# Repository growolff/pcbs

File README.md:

# pcbs
Documentación de PCBs de proyectos personales, para acceso y repositoreo remoto.

* UsainBot v1

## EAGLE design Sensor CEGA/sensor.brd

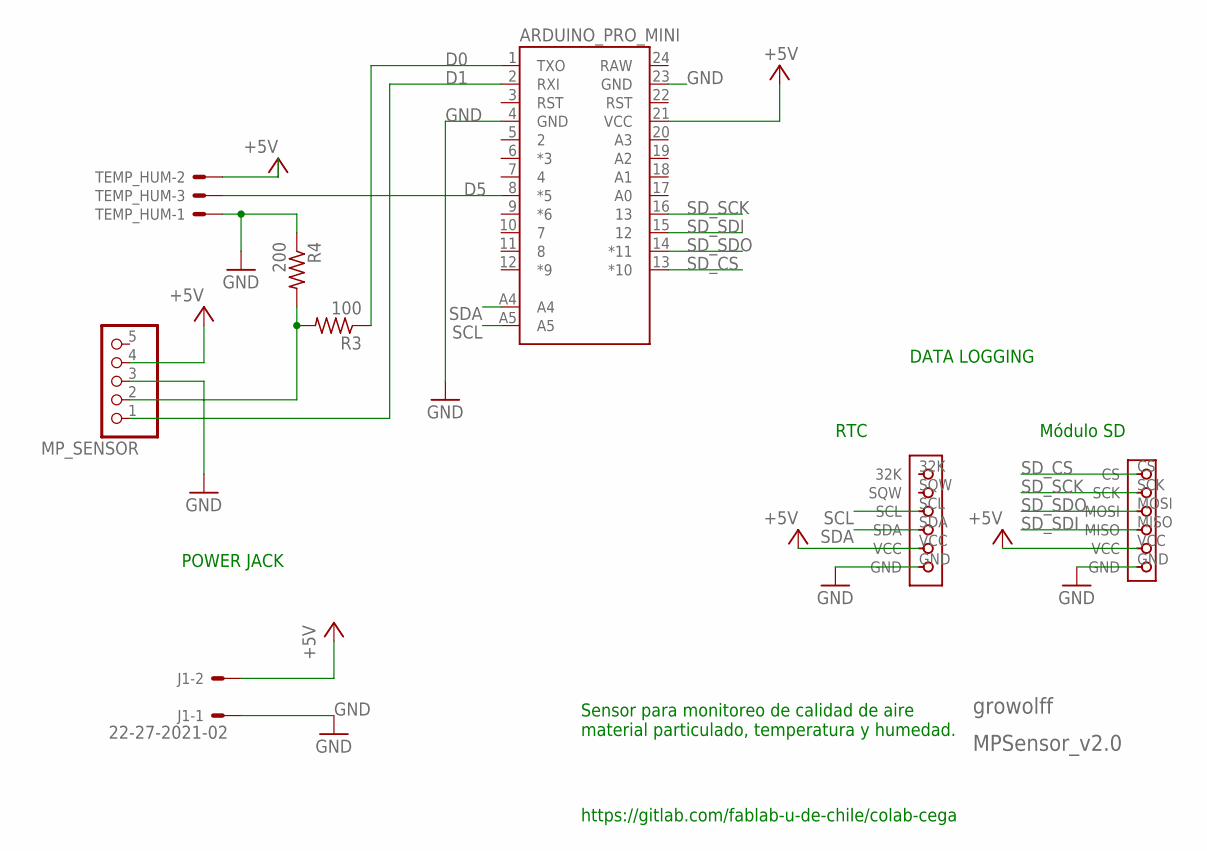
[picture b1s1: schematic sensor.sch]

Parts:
ARDUINO_PRO_MINI: PRO_MINI_CEGAPRO_MINI_MOD; ARDUINO_PRO_MINI_MOD
J1: 22-27-2021-02; 6410-02
MP_SENSOR: PINHD-1X5; 1X05
R3: 100; 0207/7
R4: 200; 0207/7
RTC: DS3231_RTC
SD_READER: MICRO_SD_READER
TEMP_HUM: 22-27-2031-03; 6410-03

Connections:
+5V: ARDUINO_PRO_MINI.21 (VCC), J1.2, MP_SENSOR.4, RTC.VCC, SD_READER.VCC, TEMP_HUM.2
D0: ARDUINO_PRO_MINI.1 (TXO), R3.1
D1: ARDUINO_PRO_MINI.2 (RXI), MP_SENSOR.1
D5: ARDUINO_PRO_MINI.8 (*5), TEMP_HUM.3
GND: ARDUINO_PRO_MINI.4 (GND), ARDUINO_PRO_MINI.23 (GND), J1.1, MP_SENSOR.3, R4.1, RTC.GND, SD_READER.GND, TEMP_HUM.1
unnamed: MP_SENSOR.2, R3.2, R4.2
RAW: ARDUINO_PRO_MINI.24 (RAW)
SCL: ARDUINO_PRO_MINI.A5, RTC.SCL
SDA: ARDUINO_PRO_MINI.A4, RTC.SDA
SD_CS: ARDUINO_PRO_MINI.13 (*10), SD_READER.CS
SD_SCK: ARDUINO_PRO_MINI.16 (13), SD_READER.SCK
SD_SDI: ARDUINO_PRO_MINI.15 (12), SD_READER.MISO
SD_SDO: ARDUINO_PRO_MINI.14 (*11), SD_READER.MOSI

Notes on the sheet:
growolff
https://gitlab.com/fablab-u-de-chile/colab-cega
Sensor para monitoreo de calidad de aire material particulado, temperatura y humedad.
MPSensor_v2.0
Módulo SD
DATA LOGGING
RTC
POWER JACK

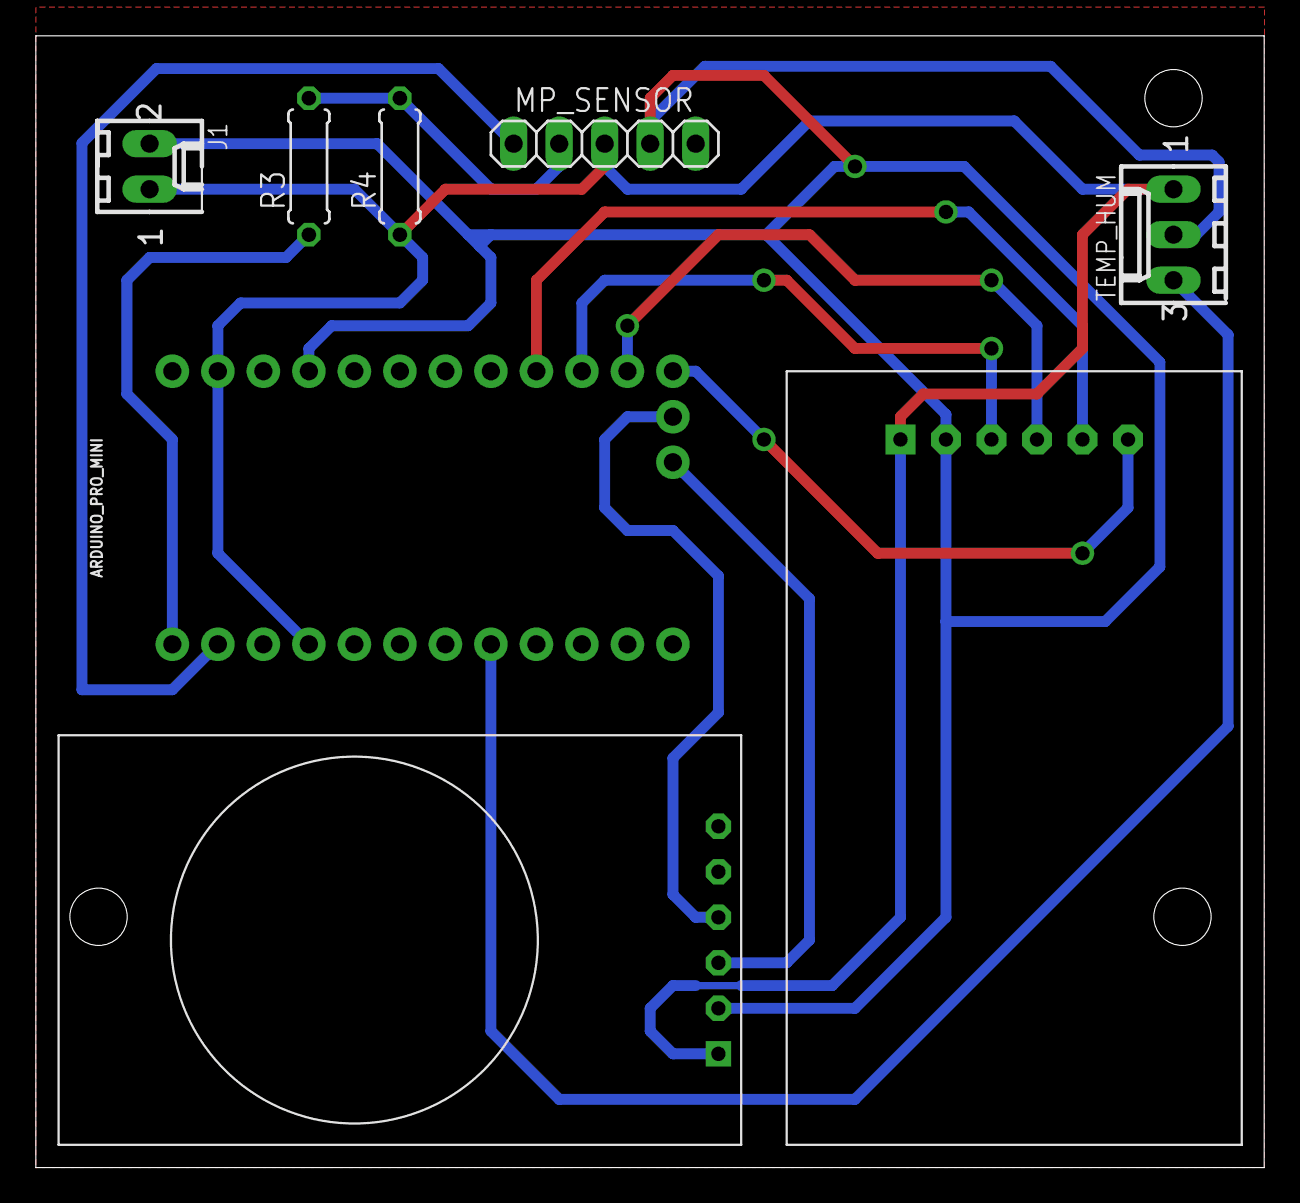
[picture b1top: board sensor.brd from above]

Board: 2 copper layers, 68.6 x 63.2 mm, 8 parts (0 on the bottom side), 12 nets.

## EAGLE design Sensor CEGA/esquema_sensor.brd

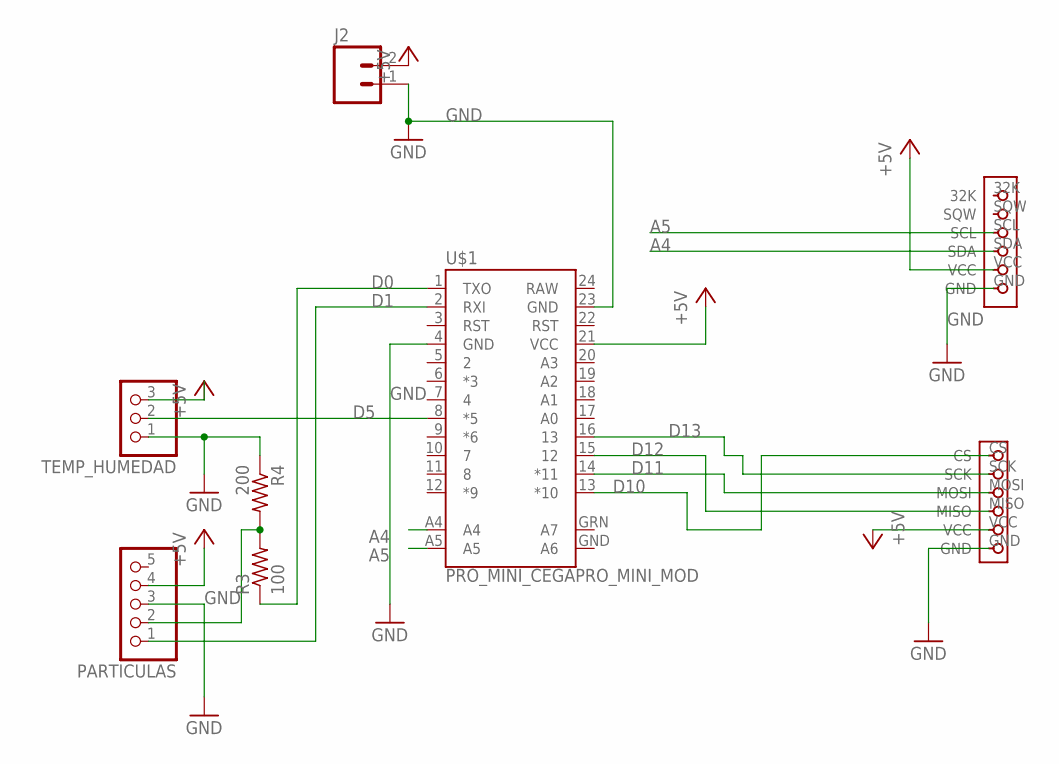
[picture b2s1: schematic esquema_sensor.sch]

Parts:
J2: M025MM; SCREWTERMINAL-5MM-2
PARTICULAS: PINHD-1X5; 1X05
R3: 100; 0207/7
R4: 200; 0207/7
RTC: DS3231_RTC
SD_READER: MICRO_SD_READER
TEMP_HUMEDAD: PINHD-1X3; 1X03
U$1: PRO_MINI_CEGAPRO_MINI_MOD; ARDUINO_PRO_MINI_MOD

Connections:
+5V: J2.2, PARTICULAS.4, RTC.VCC, SD_READER.VCC, TEMP_HUMEDAD.3, U$1.21 (VCC)
A4: RTC.SDA, U$1.A4
A5: RTC.SCL, U$1.A5
D0: R3.1, U$1.1 (TXO)
D1: PARTICULAS.1, U$1.2 (RXI)
D5: TEMP_HUMEDAD.2, U$1.8 (*5)
D10: SD_READER.CS, U$1.13 (*10)
D11: SD_READER.MOSI, U$1.14 (*11)
D12: SD_READER.MISO, U$1.15 (12)
D13: SD_READER.SCK, U$1.16 (13)
GND: J2.1, PARTICULAS.3, R4.1, RTC.GND, SD_READER.GND, TEMP_HUMEDAD.1, U$1.4 (GND), U$1.23 (GND)
unnamed: PARTICULAS.2, R3.2, R4.2
RAW: U$1.24 (RAW)

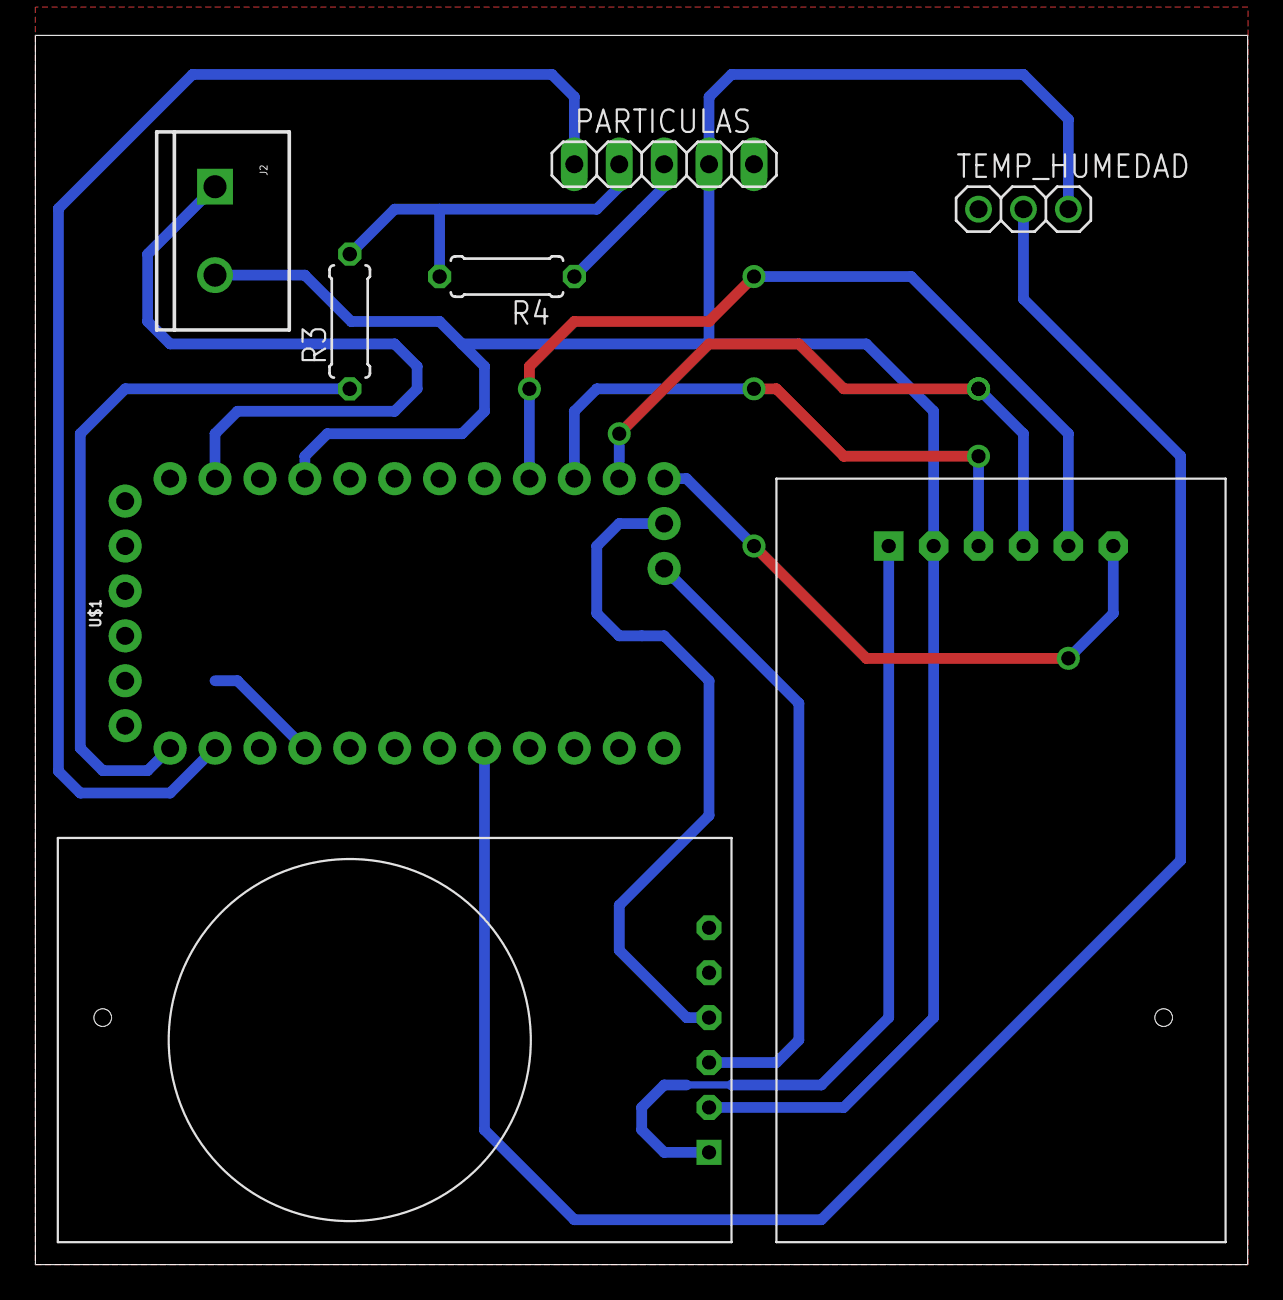
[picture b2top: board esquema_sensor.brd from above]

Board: 2 copper layers, 68.6 x 69.5 mm, 8 parts (0 on the bottom side), 12 nets.

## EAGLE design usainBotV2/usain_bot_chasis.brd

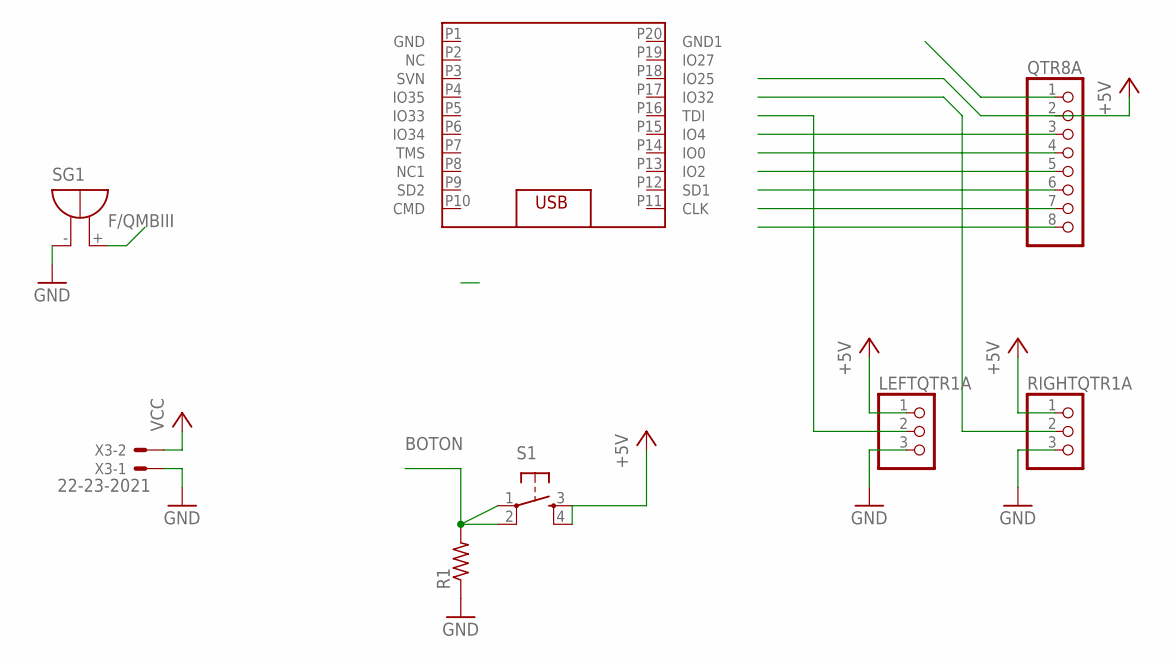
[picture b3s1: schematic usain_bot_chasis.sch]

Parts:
ESP32: ESP32_MINI_KIT
LEFTQTR1A: PINHD-1X3; 1X03
QTR8A: PINHD-1X8BIG; 1X08-BIG
R1: R-US_0207/7; 0207/7
RIGHTQTR1A: PINHD-1X3; 1X03
S1: TAC_SWITCHPTH; TACTILE-PTH
SG1: F/QMBIII
X3: 22-23-2021

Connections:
+5V: LEFTQTR1A.1, QTR8A.2, RIGHTQTR1A.1, S1.3, S1.4
BOTON: R1.2, S1.1, S1.2
GND: LEFTQTR1A.3, R1.1, RIGHTQTR1A.3, SG1.- (+), X3.1
VCC: X3.2

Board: 2 copper layers, 8 parts (0 on the bottom side), 3 nets, no tracks yet.

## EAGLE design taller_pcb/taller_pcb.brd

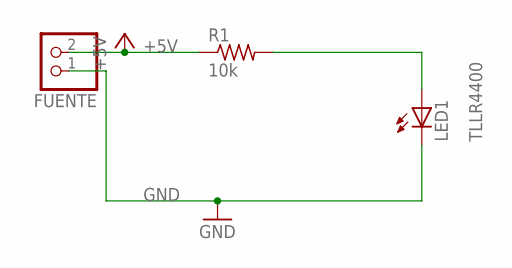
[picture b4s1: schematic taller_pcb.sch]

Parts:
FUENTE: PINHD-1X2; 1X02
LED1: TLLR4400; LED3MM
R1: 10k; 0309/12

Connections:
+5V: FUENTE.2, R1.1
GND: FUENTE.1, LED1.K (C)
unnamed: LED1.A, R1.2

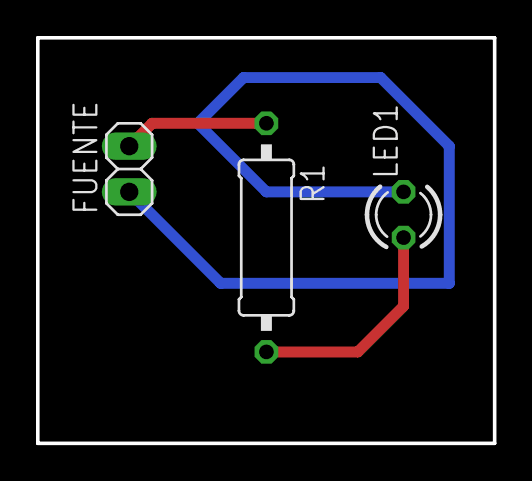
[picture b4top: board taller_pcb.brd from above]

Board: 2 copper layers, 25.4 x 22.5 mm, 3 parts (0 on the bottom side), 3 nets.

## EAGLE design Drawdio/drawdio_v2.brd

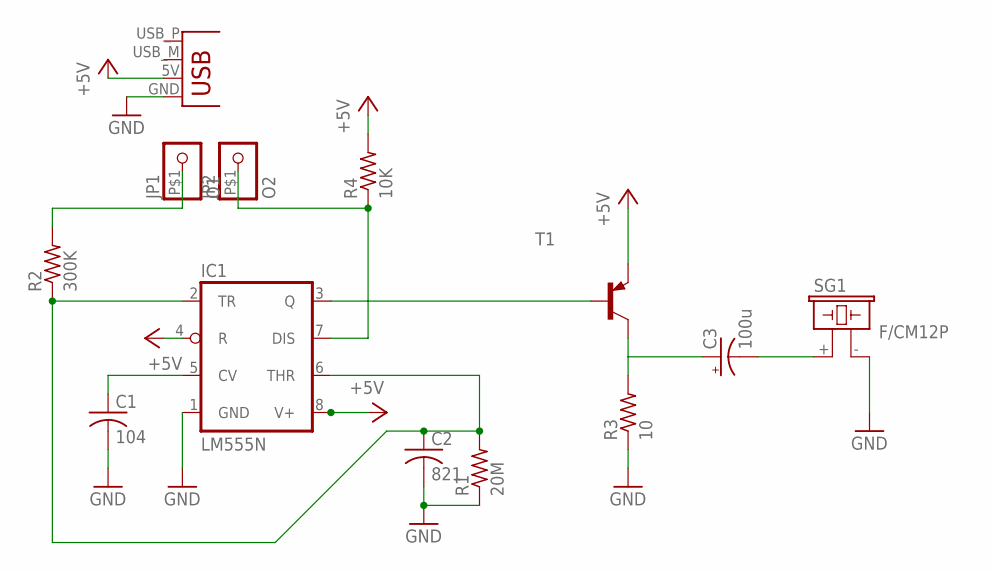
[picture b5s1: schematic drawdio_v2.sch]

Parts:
C1: 104; C025-030X050
C2: 821; C050-024X044
C3: 100u; E2,5-6E
IC1: LM555N; DIL08
JP1: O1; 1X1-BIGPOGO
JP2: O2; 1X1-BIGPOGO
R1: 20M; 0207/7
R2: 300K; 0207/7
R3: 10; 0207/7
R4: 10K; 0207/7
SG1: F/CM12P
T1: MPS2907A-PNP-TO92-CBE; TO92-CBE
X1: USBPCB; USB-A-PCB

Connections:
+5V: IC1.4 (R), IC1.8 (V+), R4.2, T1.E, X1.5V (VBUS)
GND: C1.2, C2.2, IC1.1 (GND), R1.1, R3.1, SG1.- (2), X1.GND
unnamed: C1.1, IC1.5 (CV)
unnamed: C2.1, IC1.2 (TR), IC1.6 (THR), R1.2, R2.1
unnamed: C3.-, SG1.+ (1)
unnamed: JP1.P$1, R2.2
unnamed: IC1.7 (DIS), JP2.P$1, R4.1
unnamed: IC1.3 (Q), T1.B
unnamed: C3.+, R3.2, T1.C

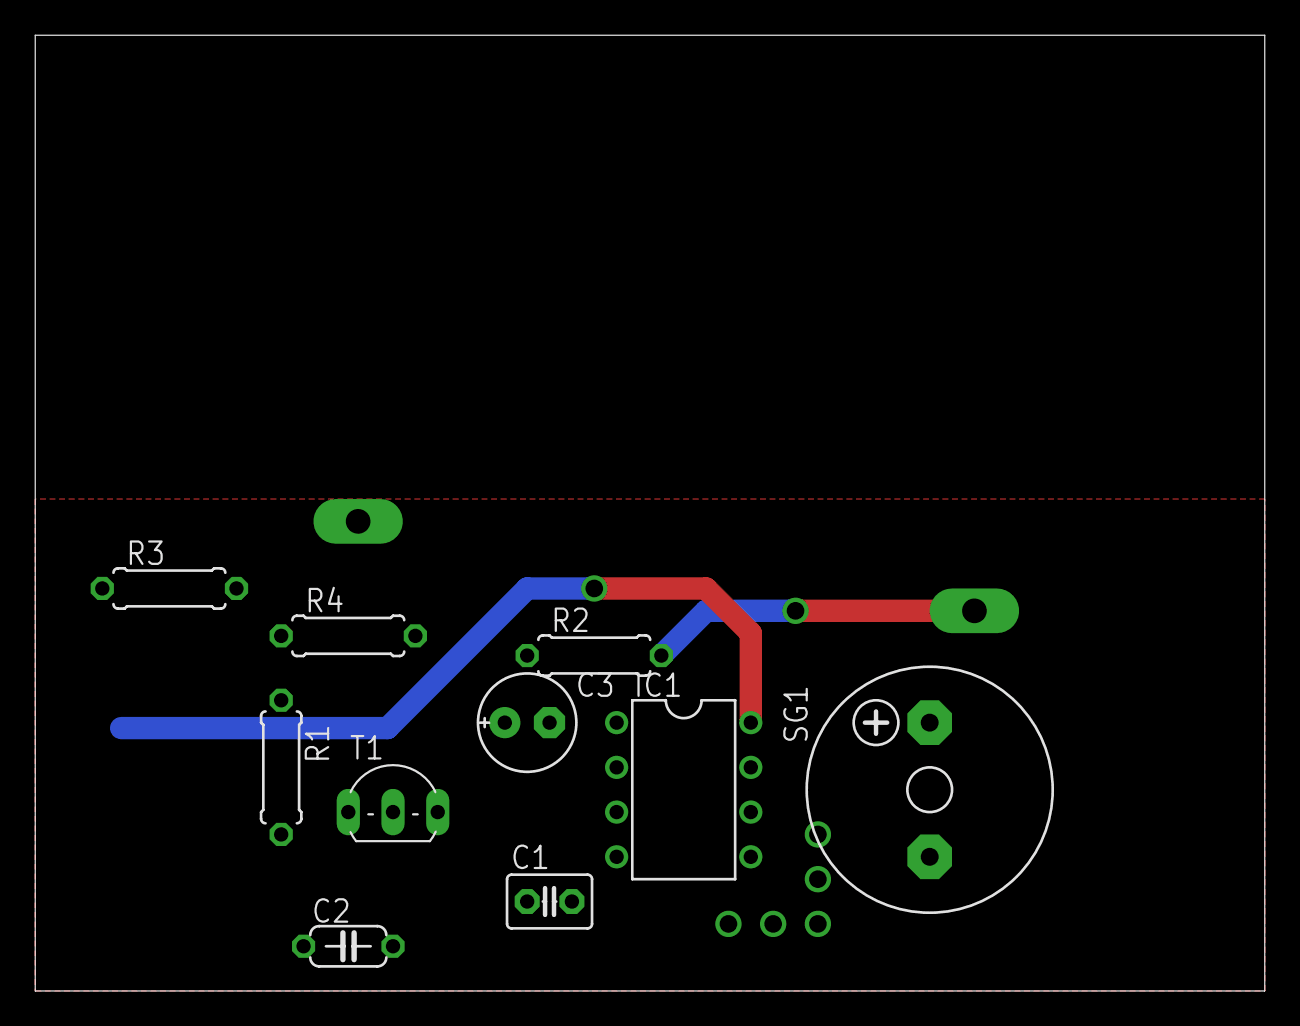
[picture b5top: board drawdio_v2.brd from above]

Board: 2 copper layers, 69.8 x 54.3 mm, 13 parts (1 on the bottom side), 9 nets.

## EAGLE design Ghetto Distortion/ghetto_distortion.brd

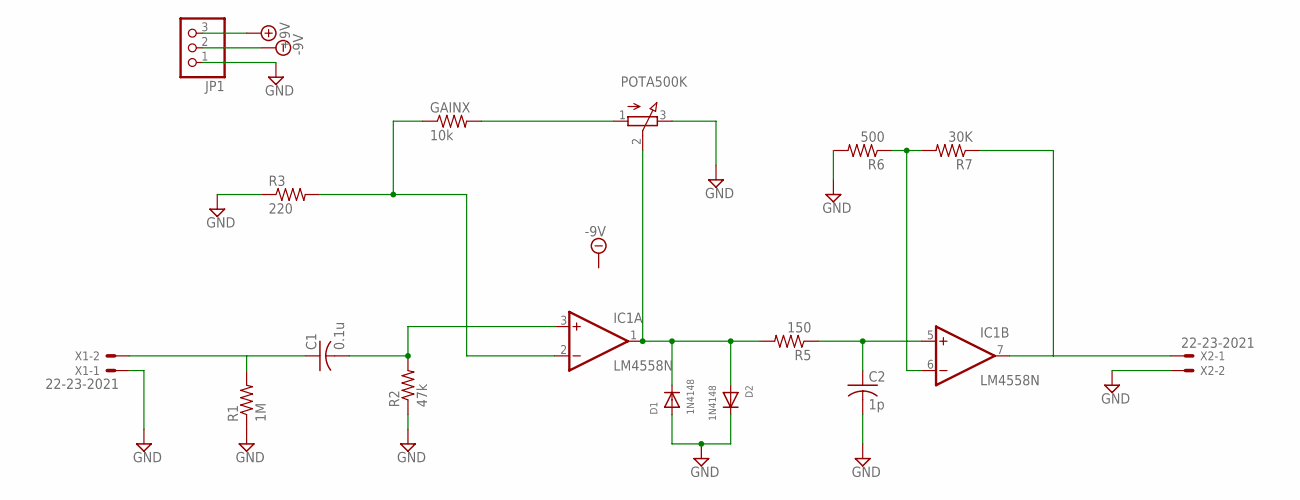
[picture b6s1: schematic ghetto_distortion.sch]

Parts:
C1: 0.1u; C050-024X044
C2: 1p; C050-024X044
D1, D2: 1N4148; DO-1N4148
GAINX: 10k; 0204/7
IC1: LM4558N; DIL08
JP1: PINHD-1X3; 1X03
POTA500K: 3RP/1610N
R1: 1M; 0204/7
R2: 47k; 0204/7
R3: 220; 0204/7
R5: 150; 0204/7
R6: 500; 0204/7
R7: 30K; 0204/7
X1, X2: 22-23-2021

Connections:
GND: C2.2, D1.A, D2.C, JP1.1, POTA500K.3 (E), R1.1, R2.1, R3.1, R6.2, X1.1, X2.2
unnamed: C1.2, IC1.3 (+IN), R2.2
unnamed: C1.1, R1.2, X1.2
unnamed: GAINX.1, IC1.2 (-IN), R3.2
unnamed: D1.C, D2.A, IC1.1 (OUT), POTA500K.2 (S), R5.2
unnamed: C2.1, IC1.5 (+IN), R5.1
unnamed: IC1.7 (OUT), R7.1, X2.1
unnamed: GAINX.2, POTA500K.1 (A)
unnamed: IC1.6 (-IN), R6.1, R7.2
V+: IC1.8 (V+), JP1.3
V-: IC1.4 (V-), JP1.2

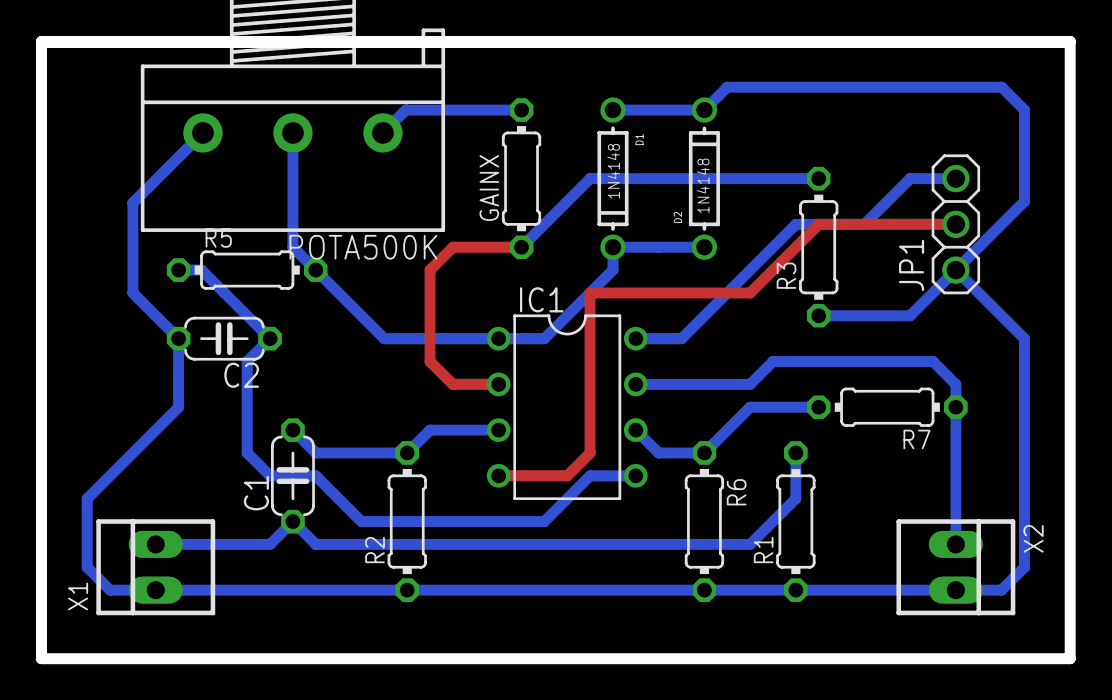
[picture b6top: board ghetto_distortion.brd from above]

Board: 2 copper layers, 57.1 x 34.3 mm, 16 parts (0 on the bottom side), 11 nets.

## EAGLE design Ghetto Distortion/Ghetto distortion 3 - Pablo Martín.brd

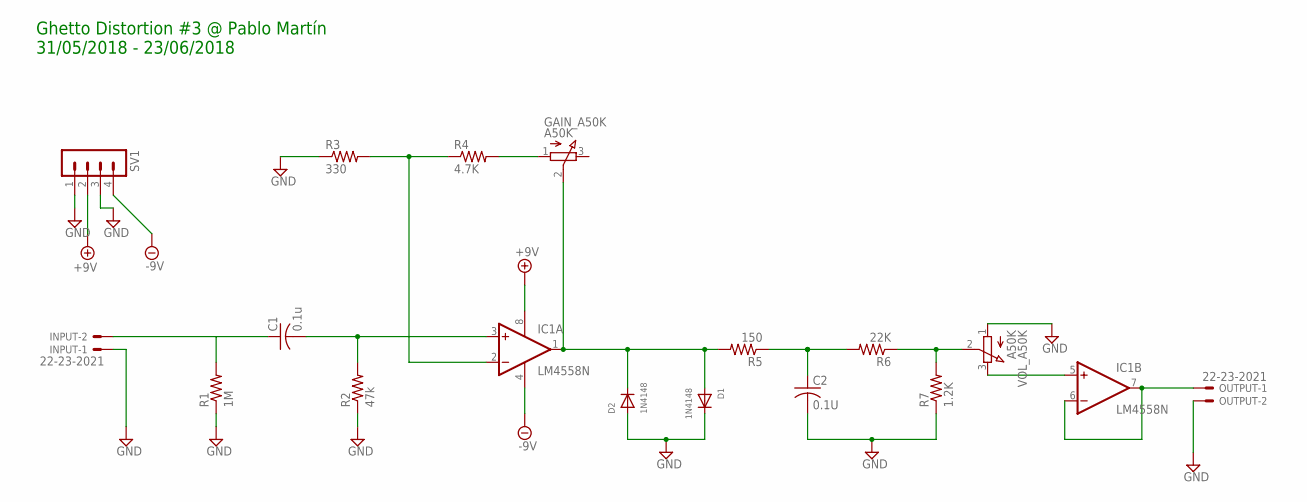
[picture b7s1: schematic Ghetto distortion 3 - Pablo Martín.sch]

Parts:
C1: 0.1u; C050-024X044
C2: 0.1U; C050-024X044
D1, D2: 1N4148; DO-1N4148
GAIN_A50K: A50K; 3RP/1610N
IC1: LM4558N; DIL08
INPUT: 22-23-2021
OUTPUT: 22-23-2021
R1: 1M; 0204/7
R2: 47k; 0204/7
R3: 330; 0204/7
R4: 4.7K; 0204/7
R5: 150; 0204/7
R6: 22K; 0204/7
R7: 1.2K; 0204/7
SV1: MA04-1
VOL_A50K: A50K; 3RP/1610N

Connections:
+9V: IC1.8 (V+), SV1.2
-9V: IC1.4 (V-), SV1.4
GND: C2.2, D1.C, D2.A, INPUT.1, OUTPUT.2, R1.1, R2.1, R3.1, R7.1, SV1.1, SV1.3, VOL_A50K.1 (A)
unnamed: C1.2, IC1.3 (+IN), R2.2
unnamed: C1.1, INPUT.2, R1.2
unnamed: IC1.2 (-IN), R3.2, R4.1
unnamed: D1.A, D2.C, GAIN_A50K.2 (S), IC1.1 (OUT), R5.2
unnamed: R6.1, R7.2, VOL_A50K.2 (S)
unnamed: IC1.5 (+IN), VOL_A50K.3 (E)
unnamed: GAIN_A50K.1 (A), R4.2
unnamed: IC1.6 (-IN), IC1.7 (OUT), OUTPUT.1
unnamed: C2.1, R5.1, R6.2

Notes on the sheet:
Ghetto Distortion #3 @ Pablo Martín 31/05/2018 - 23/06/2018

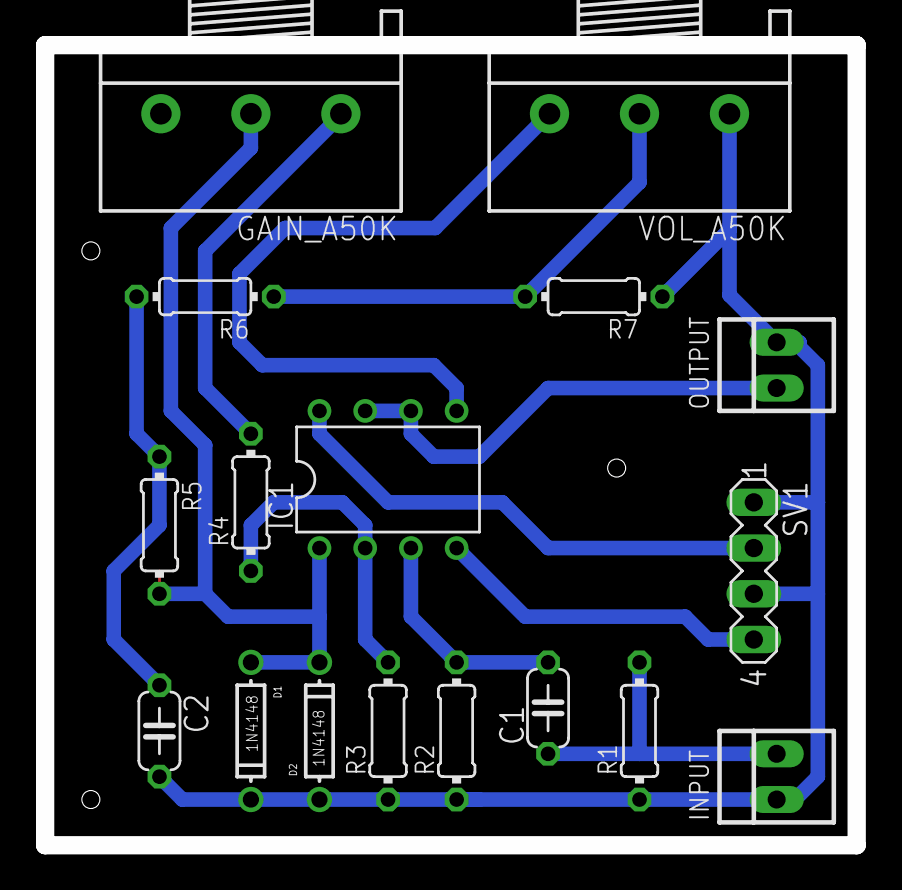
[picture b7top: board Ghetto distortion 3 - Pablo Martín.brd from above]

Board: 2 copper layers, 45.1 x 44.5 mm, 17 parts (0 on the bottom side), 12 nets.

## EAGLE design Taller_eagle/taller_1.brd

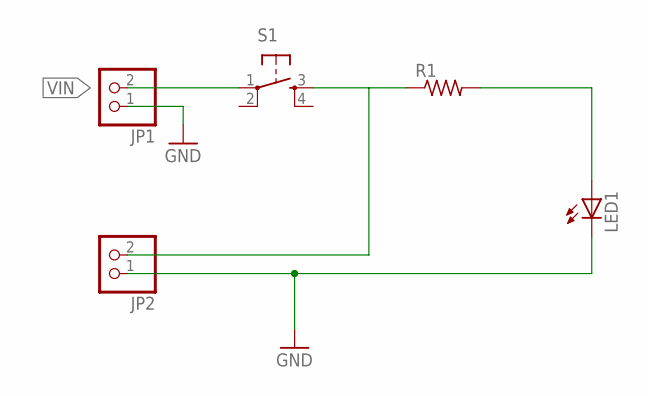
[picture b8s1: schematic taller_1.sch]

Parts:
JP1, JP2: PINHD-1X2/90; 1X02/90
LED1: LED5MM
R1: R-US_0207/15; 0207/15
S1: TAC_SWITCHPTH; TACTILE-PTH

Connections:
GND: JP1.1, JP2.1, LED1.K (C)
unnamed: JP2.2, R1.1, S1.3
unnamed: LED1.A, R1.2
VIN: JP1.2, S1.1

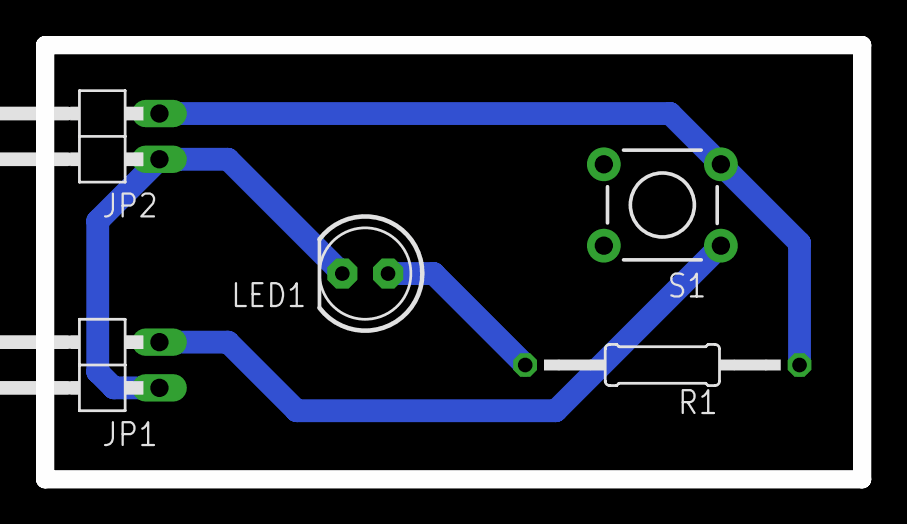
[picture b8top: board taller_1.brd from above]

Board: 2 copper layers, 45.4 x 24.1 mm, 5 parts (0 on the bottom side), 4 nets.

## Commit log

2019-08-14 sensor cega
2019-08-14 sensor cega v1, falta rutear las pistas
2019-08-20 primera versión ubot 2.0
2019-08-21 versión 1.0 del sensor en PCB
2019-08-22 carpetas ordenadas y limpias, proyectos de pcbs en este repo
2019-09-03 agregado taller pcb
2019-09-09 added fablab_uchile lib
2019-09-09 actualizado sensor cega y usain bot
2020-08-18 last version and fotos
2020-08-27 carpetas ordenaas
2020-08-27 cambio de carpetas
2021-08-11 update eagle libs
2021-08-17 add libraries
2021-08-17 se agrega openlog a la librería

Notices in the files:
parts and their libraries:
SparkFun: Licensing: CC v3.0 Share-Alike You are welcome to use this library for commercial purposes.
SparkFun-Connectors: Licensing: Creative Commons ShareAlike 4.0 International - https://creativecommons.org/licenses/by-sa/4.0
